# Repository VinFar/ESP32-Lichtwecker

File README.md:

ESP32 Lichtwäcker
===
# Introduction
This repository is about a custom built alarm clock, which wakes you up with light instead of sound. It mimics the sunrise inside your bedroom, so that you are been woken up gently and more natural. The main light source (a.k.a. wake light) is a high power LED with around 50W of power. This is plenty of power to illuminate a big room.

It features a convient Web Interface, where you configure the alarm clock.
You can set the alarm time, the rising time, the maximum LED power and much more.
When a alarm sets in, the brightness is slowly increased (configurable) until the maximum power (configurable) is reached. Then the brightness is held at this point for specific amount of time (configurable).

With the integrated button it is possible to switch off the alarm, activate a "reading light" (low brightness), activate full power or activate the last use RGB Effect.

Beside the high power LED there are 24 WS2812B RGB LED chips arranged in a circle. This makes it possible to use the alarm clock also as a mood or RGB light. It features a lot of effects, that can be selected over the Web Interface.

# Features
The alarm clock has the following features:

- **50W high power LED**
- **High efficient LED driver**
- **ESP32 to control everythin**
- **Custom PCB which implements the electronics**
- **RGB LEDs to create beautiful animations and mood lights**
- **Web Interface to configure the following settings**
  - **Alarm time for each day of the week**
  - **Brightness rising and holding time**
  - **LED power for the wake light**
  - **RGB effect for the mood light**
- **OTA Updates**
- **Alexa and Google Assistant ready ("Alexa, set the alarm light to 20%")**
- **Temperature sensor for the high power LED**
- **Aluminium heat sink with a 30mm fan for cooling**
  - **Fan can switched off, as it obviously makes noise, which is not necessarily desirable when you wake up :)**
- **All parts (beside LED heatsink) are 3D-printable**

## Main LED
___
The mainlight source is a high quality power LED from CREE (CMT2850). It features a CRI of 92, a natural color of 5000K and around 50W of power. It is mounted to the heatsink.
It is driven by an LCM-60 CC-Source from Meanwell. This LED driver has a maximum power output of 60W and can drive a current of max. 1400mA.
For dimming the LED a PWM signal from the ESP32 is used. It is coupled to via an opto-coupler, to prevent GND shifts and other interferences.

## ESP32
___
The alarm clock is powered and controlled over a ESP32. It is mounted on the PCB.

## Other features
___
### Temperature sensor
A LM335 temperature sensor is fixed to the bottom of the heatsink to measure the temperature of the of the main LED. The LM335 outputs an analog voltage which is then measured by an ADC. This method was used over a classic digital OneWire sensor, as the I²C Library is immune to context switches of FreeRTOS. Also, id prevents using a fake DS18B20, as these are very common on AliExpress, eBay etc.

### Fan & heat managment
To enable better cooling of the alarm clock a 30mm fan is used. It is controlled a PWM single, to reduce noise when the temperature is not too hot. In addition, it can completely switched off over the Web Interface.
In both cases a heat managment controls the power of the LED and the fan. The power of the LED is continously reduced, if the the temperature is higher than 70°C.
Thus, the fan can be switched off, resulting in a lower brightness of the LED.

### 

### Hardware

### Firmware

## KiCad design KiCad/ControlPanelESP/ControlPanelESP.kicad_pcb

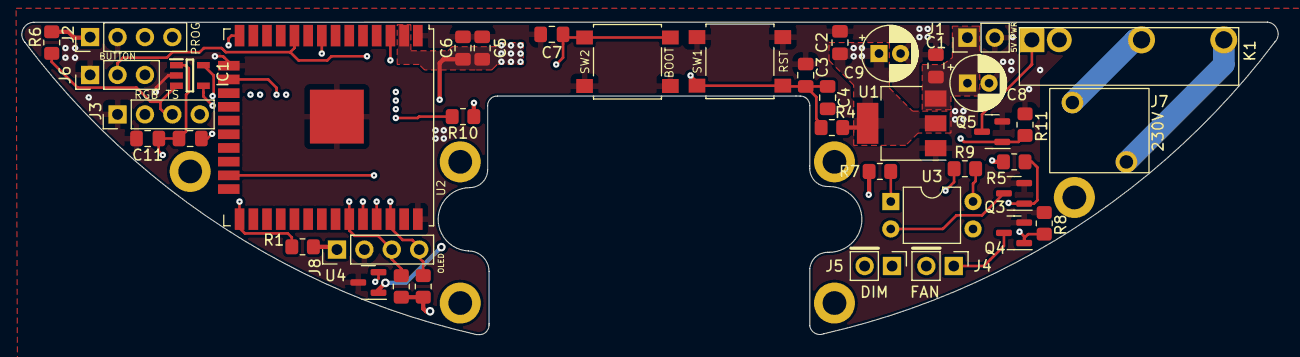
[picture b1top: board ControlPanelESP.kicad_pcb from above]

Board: 4 copper layers, 116.3 x 29.0 mm, 47 parts (0 on the bottom side), 25 nets.

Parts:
C1, C2, C5: 22u; C_0805_2012Metric_Pad1.18x1.45mm_HandSolder
C3, C4, C6, C7, C11: 100n; C_0805_2012Metric_Pad1.18x1.45mm_HandSolder
C8, C9: C_Polarized; CP_Radial_D5.0mm_P2.00mm
C10: 10u; C_0805_2012Metric_Pad1.18x1.45mm_HandSolder
H1, H2, H3, H4, H5, H6: MountingHole_Pad; MountingHole_2.2mm_M2_DIN965_Pad
IC1: MCP3221A6T-E_OT; SOT95P280X145-5N
J1, J4, J5: Conn_01x02_Male; PinHeader_1x02_P2.54mm_Vertical
J2, J3, J8: Conn_01x04_Male; PinHeader_1x04_P2.54mm_Vertical
J6: Conn_01x03_Male; PinHeader_1x03_P2.54mm_Vertical
J7: 2086-3122
K1: DIPxx-1Axx-11x; HF49FD-005-1H
Q3, Q4, Q5: Q_NMOS_GSD; SOT-23
R1, R4, R5, R8, R10, R11: 10k; R_0805_2012Metric_Pad1.20x1.40mm_HandSolder
R3, R12: 4k7; R_0805_2012Metric_Pad1.20x1.40mm_HandSolder
R6: 5.1k; R_0805_2012Metric_Pad1.20x1.40mm_HandSolder
R7, R9: 1k; R_0805_2012Metric_Pad1.20x1.40mm_HandSolder
SW1, SW2: SW_Push; SW_SPST_B3S-1000
U1: AMS1117-3.3; SOT-223-3_TabPin2
U2: ESP32-WROOM-32U
U3: LTV-817; DIP-4_W7.62mm
U4: MCP1541-TT; SOT-23

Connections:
5V: C1.1, C8.1, J1.1, J2.1, J3.4, J4.2, J6.3, K1.6, R5.1, R6.1, R7.1, R10.1, U1.3 (VI), U4.1 (Vin)
+3V3: C2.1, C5.2, C6.2, C9.1, J8.1, R1.1, R3.1, R4.1, R12.1, U1.2 (VO), U2.2 (VDD)
/230V: J7.1, K1.7
/230V1: J7.2, K1.1
BUTTON: J6.2, R10.2, U2.10 (IO25)
EN: C3.1, C4.2, R4.2, SW1.2, U2.3 (EN)
FAN: Q4.1 (G), R8.1, U2.14 (IO12)
GND: C1.2, C2.2, C3.2, C4.1, C5.1, C6.1, C7.2, C8.2, C9.2, C10.2, C11.2, IC1.2 (VSS), J1.2, J2.2, J3.1, J6.1, J8.2, Q3.2 (S), Q4.2 (S), Q5.2 (S), R8.2, R11.2, SW1.1, SW2.2, U1.1 (GND), U2.1 (GND), U2.15 (GND), U2.38 (GND), U2.39 (GND), U4.3 (Vss)
IO0: C7.1, R1.2, SW2.1, U2.25 (IO0)
LED: Q3.1 (G), R5.2, U2.16 (IO13)
unnamed: C10.1, C11.1, IC1.1 (VDD), U4.2 (Vout)
unnamed: J4.1, Q4.3 (D)
unnamed: J5.1, U3.3
unnamed: J5.2, R9.2
unnamed: K1.2, Q5.3 (D)
unnamed: Q3.3 (D), U3.2
unnamed: R7.2, U3.1
unnamed: R9.1, U3.4
RX_ESP32: J2.3, U2.34 (RXD0/IO3)
Relay: Q5.1 (G), R11.1, U2.23 (IO15)
SCL: IC1.5 (SCL), J8.4, R12.2, U2.36 (IO22)
SDA: IC1.4 (SDA), J8.3, R3.2, U2.33 (IO21)
TEMPSENSOR: IC1.3 (AIN), J3.3, R6.2
TX_ESP32: J2.4, U2.35 (TXD0/IO1)
WS2812: J3.2, U2.8 (IO32)

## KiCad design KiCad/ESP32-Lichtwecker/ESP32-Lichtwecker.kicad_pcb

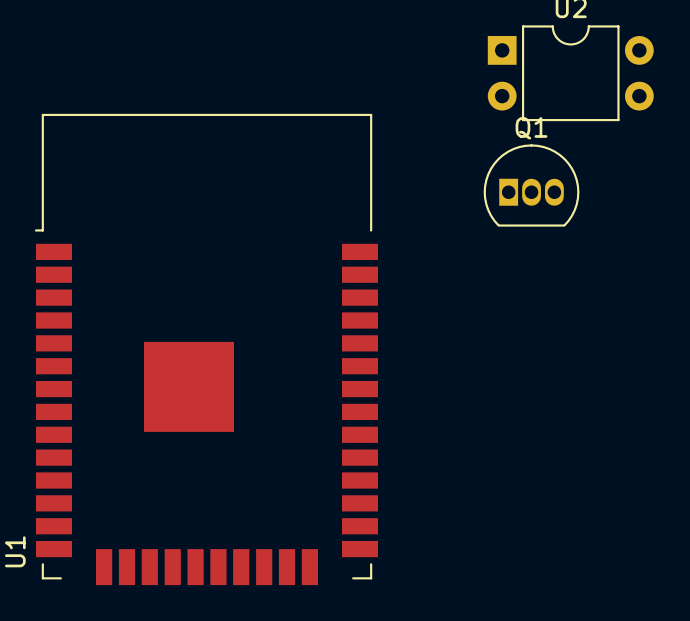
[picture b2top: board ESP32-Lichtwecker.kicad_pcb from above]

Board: 2 copper layers, 3 parts (0 on the bottom side), 3 nets, no tracks yet.

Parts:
Q1: BC547; TO-92_Inline
U1: ESP32-WROOM-32
U2: LTV-817; DIP-4_W7.62mm

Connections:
GND: Q1.3, U2.2
unnamed: Q1.1, U2.1
unnamed: U1.1, U1.15, U1.38, U1.39

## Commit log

2021-12-09 add: gitignore
2021-12-09 add: platformio init
2021-12-09 add: Init of Debug Functionality
2021-12-09 add: .c .h pair for Wifi
2021-12-11 add: Connect to Wifi, get NTP Time from Server
2021-12-11 add: daylight saving time
2021-12-11 add: print SSID and IP Address when connected to WiFi
2021-12-11 moved configTzTime to myRTC.cpp
2021-12-11 add: PWM for WakeLight and Fan
2021-12-17 add: kicad project
2021-12-17 add: debug prefixes for WEBUI
2021-12-17 add: first test of WebUI
2021-12-18 add: Dynamic creation of Tabs for different Alarms
2021-12-18 add: .cpp, .h pair for AlarmTask
2021-12-18 add: Tabs for all Weekdays, Dynamic switching on/off of Alarms for each weekday
2021-12-20 add: Function for setting Switcher State, set Switcher to correct state at init
2021-12-21 add: Preferences for Alarms struct
2021-12-21 add: test for Select of Waking Hours
2021-12-25 add: Number input for wake time with callback
2021-12-25 add: Save button for Wake Time, Read Wake Time from NVS on Reset
2021-12-28 working Alarm Trigger, Global On/Off Switch
2021-12-28 add: Function to set Power for LED Wake light
2021-12-28 add: function for saving prefs to NVS
2021-12-28 add: TemperatureSensor, TemperaturTask
2021-12-28 add: Temperature report in Status Tab
2021-12-29 add: PWM Limit for LED depending on Temp of LED
2021-12-29 re activated Reset of LED PWM afters setting pwm level for Wake Light
2021-12-29 offset for PWM of 11 and lower slope to reach 100%
2021-12-29 add: Callback for Time Interval slider
2021-12-29 add: Set correct saved value to GUI for time interval and led power
2021-12-29 add: Save Time Interval to Alarms struct
2021-12-29 First working Version: V0.1
2021-12-29 add: DutyCycle value in Status Tab
2021-12-30 ch: moved DnsServer Process next request into loop()
2021-12-31 working reliable autoConnect
2021-12-31 removed comment
2021-12-31 fixed wrong LED Power Label
2021-12-31 add: LED Power Off Timer after Wake Rising
2021-12-31 add: Debug print statement when saving Alarms struct to NVS
2022-01-02 add: PWM for FAN
2022-01-02 forgot to uncomment line
2022-01-02 add: Button
2022-01-02 Abort Alarm with Button Single Click
2022-01-02 add: Button Clock for Reading Light On/Off
2022-01-02 add: increase/decrease LED Read light with long button press
2022-01-05 add: NeoPixel
2022-01-08 refactored AlarmTask code
2022-01-08 removed AlarmGetAlarm function
2022-01-08 fixed code for warning
2022-01-08 removed print statement
2022-01-09 updated to ESPUI 2.1.0
2022-01-09 add: Control Sliders for RGB
2022-01-09 removed Debug print statement
2022-01-09 add: Selector and Function ptr for RGB Effect
2022-01-09 Implemented two RGB Effects with TaskRestart
2022-01-09 add: Strobe
2022-01-09 add: Effect implementation over WS2812FX
2022-01-10 moved ws2812fx.service() to IdleTaskHook
2022-01-10 deactivate RGB Effect with Button Click
2022-01-19 add: Google Home + Alexa support
2022-01-21 add: gitignore for Sinric Credentials
2022-01-22 add: Color Selection over Google Home
2022-01-30 removed old KiCad project
2022-01-30 first version of schematic
2022-01-31 untracked file
2022-01-31 update gitignore
2022-01-31 untracked zip files
2022-01-31 added symbol for relay
2022-02-03 add: gitignore for Kicad
2022-02-03 removed kicad file from tracking
2022-02-03 initial version of PCB
2022-09-13 second version
2022-09-13 fixed espressif core at 3.4.0
2022-09-13 Dutycycle was inverted
2022-09-13 AlarmStatus preferences were not found
2022-09-13 extensions update
2022-09-13 renamed NeoPixel Function from setAll to NeoPixelsetAll
2022-09-13 add: NeoPixelSetBrightness
2022-09-13 use different mechanism for setting NeoPixel Colors
2022-09-13 outsourced Sinric Credentials to "SinricCredentials.h"
2022-09-13 add: Sinric Smart Function "SetColor"
2022-09-13 error check on AlarmRisingTime Set
2022-09-13 add: NeoPixelAllOff
2022-09-13 set NeoPixel off when Reading Light is switched off
2022-09-14 add: OTA Update Prototype
2022-09-14 add: exception decoder to monitor filter of pio
2022-09-14 use min_spiffs.csv as partition table
2022-09-14 add: OTA to DEBUG output
2022-09-14 OTA working without other components
2022-09-14 removed some lines that were used for testing
2022-09-14 ch: OTA Port to 3456
2022-09-14 OTA Update working with other components
2022-09-14 add: fade effect when ESP is booting and acquiring WiFi
2022-09-14 add: Booting and Error Status over NeoPixel, Feedback over NeoPixel when usin WebUI
2022-09-14 fix: Reading Light PWM value was too low
2022-09-14 ch: do not discard PWM increase interval of 0
2022-09-14 add: report current led brightness back to Sinric
2022-09-15 fix: use loop to update NeoPixel
2022-09-15 v1.0.0.0
2022-09-16 add: only set global RTC Time when obtaining NTP Time was successfull
2022-09-16 checking alarm every 30s, rather than 59s
2022-09-16 increase stack size of every task to 8KB
2022-09-24 ch: deactivated continous slider, moved DNS Processing Request to dedicated Task
2022-09-24 ch: Serial Baudrate to 1M, deactivated Sinric for testing
2022-09-24 ch: better debug print statements for LED Power Slider
2022-09-24 add: Debug print statement when maximum power of LED was reduced due to too high temp of led
2022-09-24 add: debug print statements for Temp sensor
2022-09-24 add: else statement and TempSensorOKCallback
2022-09-24 ch: request temperature to end of loop right before TaskDelay
2022-09-24 forgot line for last commit
2022-09-24 add: increased stack size of TaskWebUI and TaskSNTP to 8KB
2022-09-24 add: macro for disabling Sinric (not working yet)
2022-09-24 ch: changed Serial Baudrate in platform.io
2022-09-24 v1.1.0.0
2022-09-26 add: oneWire reset and delay before init of DS18B20
2022-09-26 add: Temperature Sensor Tick for implementation in loop()
2022-09-26 add: removed creation of TaskTemperature
2022-09-26 changes to TaskTemperature (obsolete)
2022-09-26 add: TempSensorTick call in loop()
2022-09-26 add: delete TaskWebUI after init of WebUI is finished
2022-09-26 v1.1.0.3
2022-09-26 add: FreeRTOS Timer as Watchdog for Temp Sensor, reset oneWire when expired, do not set Wake LED on Temp Sensor Error
2022-09-26 fix: removed parameter n from getPixelColorHSV, was not used
2022-09-26 refactored NeoPixel.c, fixed NeoPixelSetColorForAnimation
2022-09-26 working watchdog for temp sensor
2022-09-26 add: double click for 100% Power, triple click for ESP Reset
2022-09-26 v1.1.0.4
2022-09-26 TempSensor not working due to fake DS18B20
2022-09-26 set AlarmTask Prio to 1 (low)
2022-09-26 add: correct formatting for DutyCycle value
2022-09-26 ch: changed TaskWebUI Prio to 2 (mid)
2022-09-26 ch: reactivated SinricPro
2022-09-26 ignore extension.json for project
2022-09-26 add: SimpleCLI to project
2022-09-26 add: CLI .c/.h pair to project
2022-09-26 add: Husarnet to project
2022-09-26 add: init CLI header file
2022-09-26 add: prototypes for CLI
2022-09-26 add: Debug prefix for CLI
2022-09-26 add: forgot one tab
2022-09-26 fix: forgot to increment array size of Debug Prefixes
2022-09-27 fix: renamend CLI.c to CLI.cpp
2022-09-27 add: CLI working locally, Port 8001
2022-09-30 fix: removed extra Readout of Temp Sensor over loop()
2022-09-30 v1.1.0.5
2022-10-08 V2.0 of PCB
2022-10-09 finalized PCB
2022-10-09 finalized PCB again
2022-10-09 add: OLED Display Connector, some markers
2022-10-09 add: OLED Display Header
2022-10-23 ch: MCP1541 as voltage reference for ADC
2022-11-23 add to gitignore: compile_commands.json
2022-11-23 add: Temperature Sensor with LM335 and ADC
2022-11-23 add: MeanBuffer for ADC
2022-11-23 working Temp Sensor with ADC and LM335
2022-11-23 add: Relay ON/OFF for LED CC Source
2022-11-24 removed DEBUG_PRINT statement
2022-11-24 v1.2.0.0
2022-11-26 add: Inventor Files to gitignore
2022-11-26 add: 3D Models
2022-11-26 add: pictures
2022-11-26 add more pictures
2022-11-26 First verson of ReadMe
2022-11-26 updated 3D Model for lower part
2022-12-18 add: first version of ReadMe
2022-12-18 add: kicad lockfile to gitignore
2022-12-18 changed 3D Models for upper and lower part
2022-12-18 add: adafruit library for SSD OLED
2022-12-21 working OLED Display
2022-12-23 working display
2022-12-23 changing temperature and fan settings for LED cooling
2022-12-23 fix: value for LED Timer OFF was not stored in NVS
2022-12-23 more text on display
